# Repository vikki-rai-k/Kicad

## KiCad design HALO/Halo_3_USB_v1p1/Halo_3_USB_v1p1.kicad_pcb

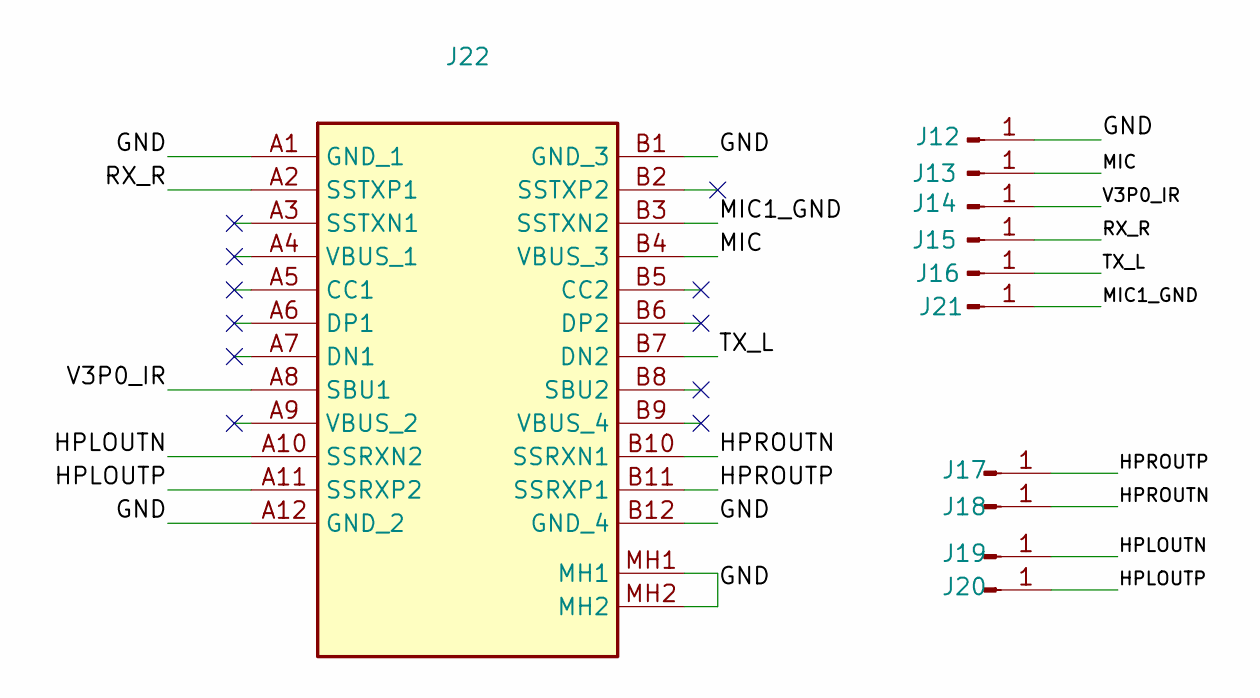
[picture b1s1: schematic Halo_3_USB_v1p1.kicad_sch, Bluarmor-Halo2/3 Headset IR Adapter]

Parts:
J12, J13, J14, J15, J16, J17, J18, J19, J20, J21: Conn_01x01_Pin; Test_Point_1.5mm_SMD_Tiny
J22: Shouhan_TypeC_24_vertical; Mouser Part Number 523-GSB3CN1130DSHR

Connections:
/GND: J12.1, J22.A1 (GND_1), J22.A12 (GND_2), J22.B1 (GND_3), J22.B12 (GND_4), J22.MH1, J22.MH2
/HPLOUTN: J19.1, J22.A10 (SSRXN2)
/HPLOUTP: J20.1, J22.A11 (SSRXP2)
/HPROUTN: J18.1, J22.B10 (SSRXN1)
/HPROUTP: J17.1, J22.B11 (SSRXP1)
/MIC: J13.1, J22.B4 (VBUS_3)
/MIC1_GND: J21.1, J22.B3 (SSTXN2)
/RX_R: J15.1, J22.A2 (SSTXP1)
/TX_L: J16.1, J22.B7 (DN2)
/V3P0_IR: J14.1, J22.A8 (SBU1)

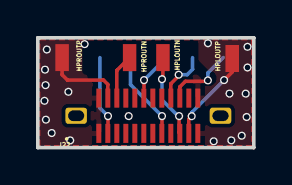
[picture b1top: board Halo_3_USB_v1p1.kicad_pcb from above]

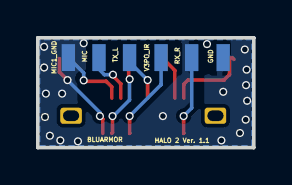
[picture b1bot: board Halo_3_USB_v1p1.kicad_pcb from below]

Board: 2 copper layers, 12.0 x 6.1 mm, 11 parts (6 on the bottom side), 10 nets.

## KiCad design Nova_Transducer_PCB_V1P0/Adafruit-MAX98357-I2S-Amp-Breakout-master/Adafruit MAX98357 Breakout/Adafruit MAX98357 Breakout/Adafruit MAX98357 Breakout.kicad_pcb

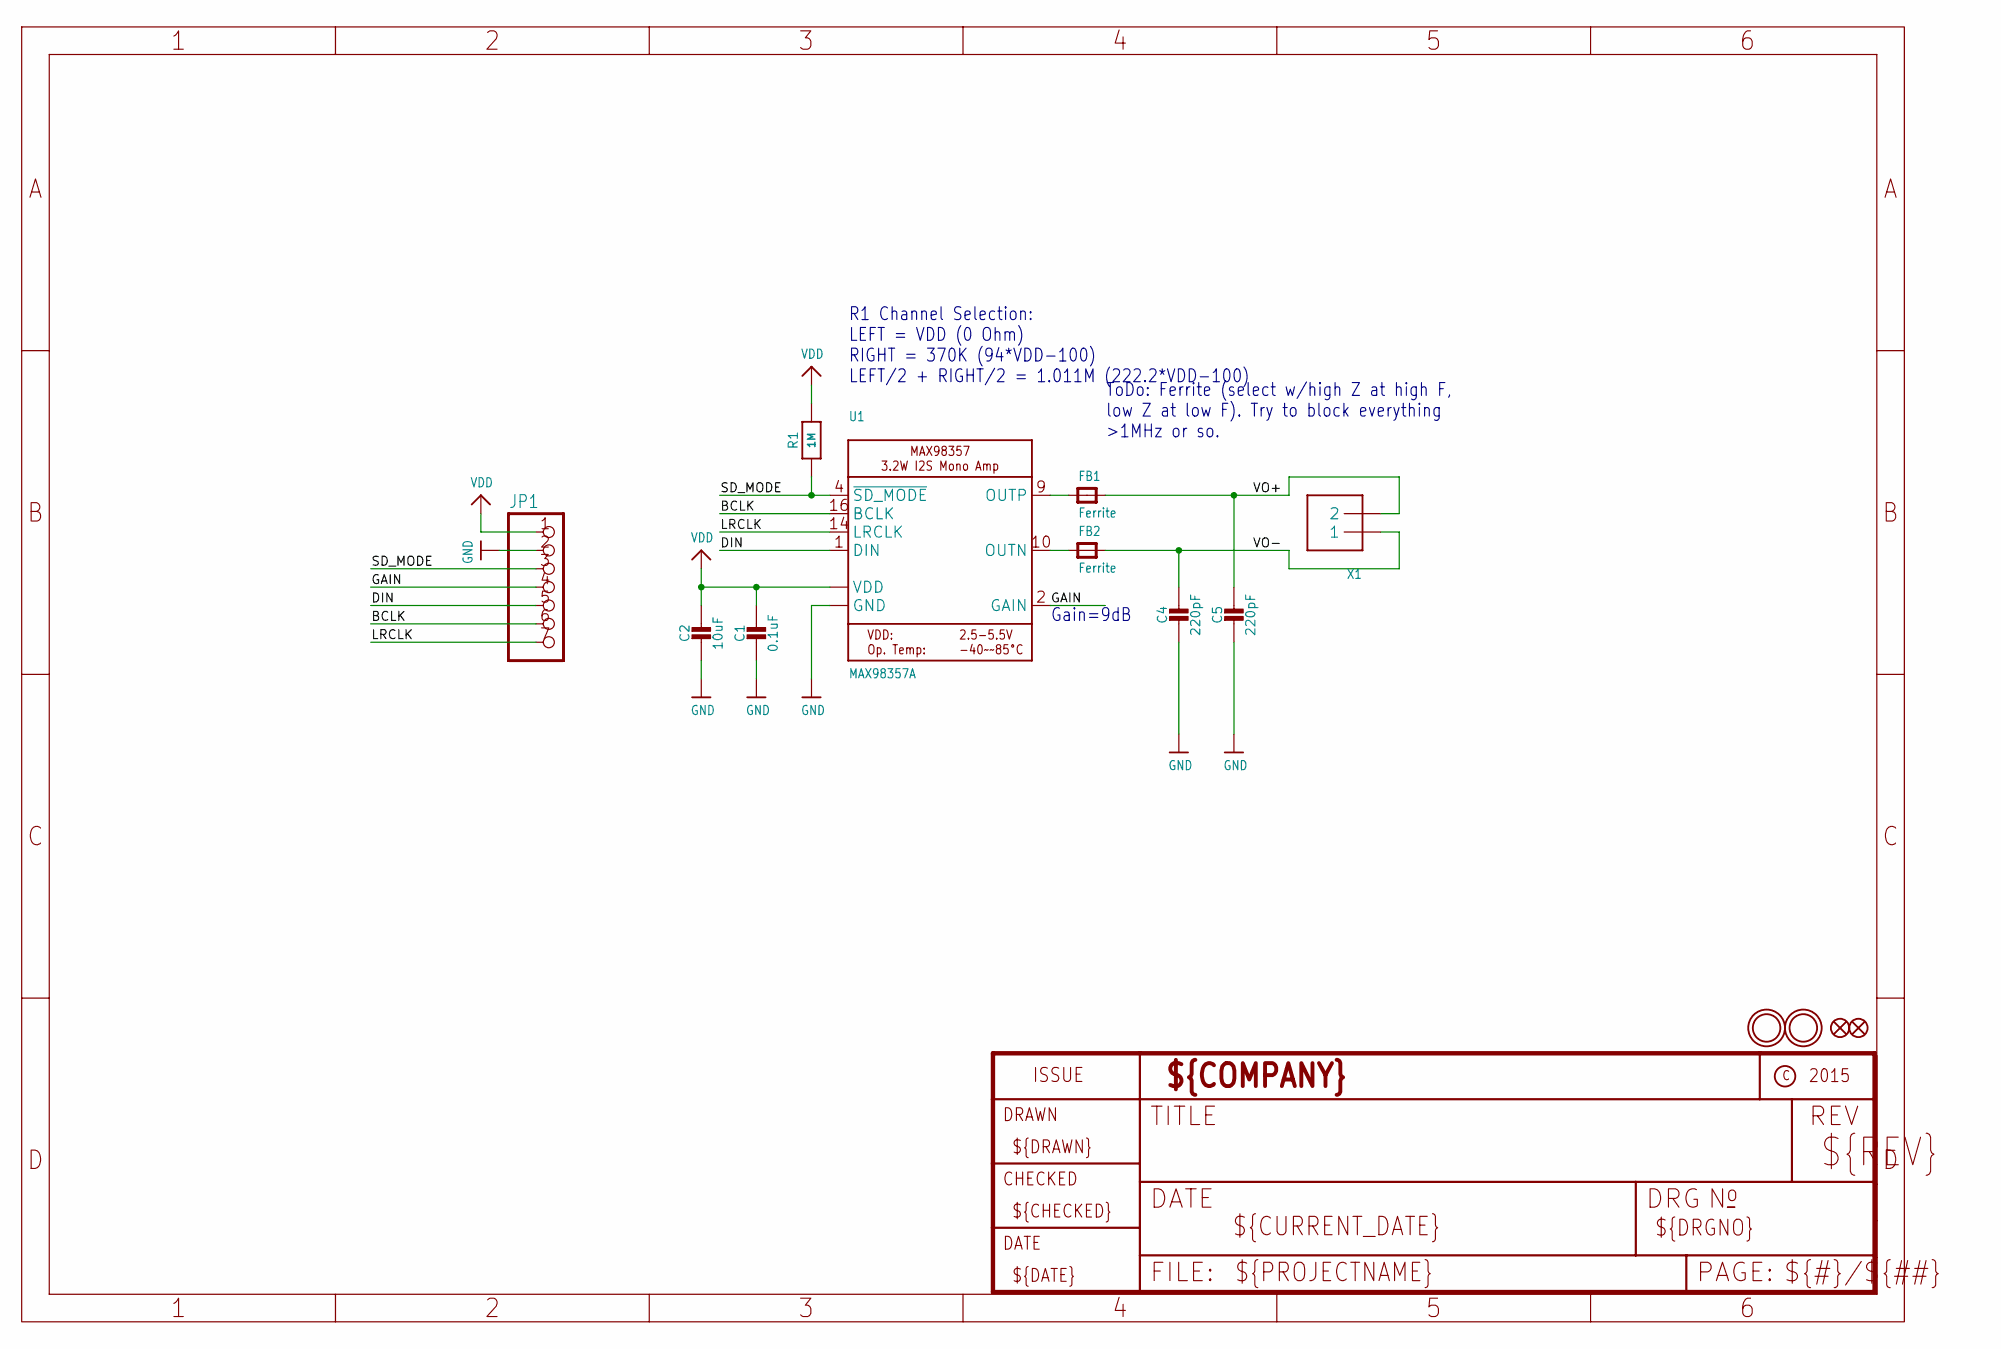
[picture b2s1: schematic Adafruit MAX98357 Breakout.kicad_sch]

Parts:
C1: 0.1uF; 0805-NO
C2: 10uF; 0805-NO
C4, C5: 220pF; 0805-NO
FB1, FB2: Ferrite; 0805-NO
FID1, FID2: FIDUCIAL""; FIDUCIAL_1MM
JP1: HEADER-1X7THICKER; 1X07_ROUND_76
R1: 1M; 0805-NO
U1: MAX98357A; QFN16_3MM
U$9, U$10: MOUNTINGHOLE2.5; MOUNTINGHOLE_2.5_PLATED
X1: TERMBLOCK_1X2; TERMBLOCK_1X2-3.5MM

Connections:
BCLK: JP1.6, U1.16 (BCLK)
DIN: JP1.5, U1.1 (DIN)
GAIN: JP1.4, U1.2 (GAIN)
GND: C1.2, C2.2, C4.2, C5.2, JP1.2, U1.3 (GND), U1.11 (GND), U1.15 (GND), U1.THERMAL (GND)
LRCLK: JP1.7, U1.14 (LRCLK)
unnamed: FB2.1, U1.10 (OUTN)
unnamed: FB1.1, U1.9 (OUTP)
SD_MODE: JP1.3, R1.1, U1.4 (~SD_MODE)
VDD: C1.1, C2.1, JP1.1, R1.2, U1.7 (VDD), U1.8 (VDD)
VO+: C5.1, FB1.2, X1.2
VO-: C4.1, FB2.2, X1.1

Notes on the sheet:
Gain=9dB
R1 Channel Selection: LEFT = VDD (0 Ohm) RIGHT = 370K (94*VDD-100) LEFT/2 + RIGHT/2 = 1.011M (222.2*VDD-100)
ToDo: Ferrite (select w/high Z at high F, low Z at low F). Try to block everything >1MHz or so.

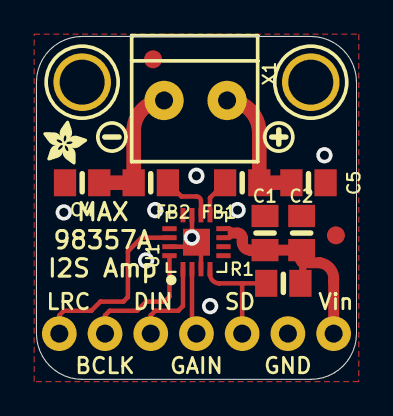
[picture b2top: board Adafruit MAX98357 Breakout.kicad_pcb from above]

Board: 2 copper layers, 17.8 x 19.0 mm, 18 parts (1 on the bottom side), 11 nets.

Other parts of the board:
U$6: SYMBOL_PLUS
U$11: SYMBOL_MINUS
U$14: ADAFRUIT_2.5MM
U$15: PCBFEAT-REV-040

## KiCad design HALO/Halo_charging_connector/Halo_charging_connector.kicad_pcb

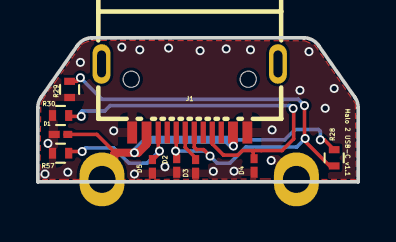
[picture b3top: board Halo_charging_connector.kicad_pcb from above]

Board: 2 copper layers, 17.8 x 8.0 mm, 12 parts (0 on the bottom side), 6 nets.

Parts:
D1, D2, D3, D4, D5: ESD5451X2TR
J1: TYPE-C 16PFS 2JCB1.6-H7.45 IPX8; USB-SMD_TYPE-C-16PFS-2J-H7.45-IPX8
R28: 60.4K; R_0402
R29: 10K; R_0402
R30, R57: 5.1K; R_0402
U1, U2: -; Halo_2_USBC_Charging_PCB_Castellated_holes

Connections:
/CC1: D4.2 (A2), J1.A5 (CC1), R30.1
/CC2: D5.2 (A2), J1.B5 (CC2), R57.1
/DN: D3.2 (A2), J1.A7 (DA_N)
/DP: D2.2 (A2), J1.A6 (DA_P), J1.B6 (DB_P), R28.2, R29.1
/GND: D1.1 (A1), D2.1 (A1), D3.1 (A1), D4.1 (A1), D5.1 (A1), J1.B1A12 (GNDB), J1.B12A1 (GNDA), R29.2, R30.2, R57.2, U2.1
/VUSB: D1.2 (A2), J1.A4B9 (VBUS_A), J1.A9B4 (VBUS_B), R28.1, U1.1

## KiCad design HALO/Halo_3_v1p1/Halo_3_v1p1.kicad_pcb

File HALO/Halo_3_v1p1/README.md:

# MagnaRox

## Getting started

To make it easy for you to get started with GitLab, here's a list of recommended next steps.

Already a pro? Just edit this README.md and make it your own. Want to make it easy? [Use the template at the bottom](#editing-this-readme)!

## Add your files

- [ ] [Create](https://docs.gitlab.com/ee/user/project/repository/web_editor.html#create-a-file) or [upload](https://docs.gitlab.com/ee/user/project/repository/web_editor.html#upload-a-file) files
- [ ] [Add files using the command line](https://docs.gitlab.com/ee/gitlab-basics/add-file.html#add-a-file-using-the-command-line) or push an existing Git repository with the following command:

```
cd existing_repo
git remote add origin https://gitlab.com/bluarmor_hw_dev/magnarox.git
git branch -M main
git push -uf origin main
```

## Integrate with your tools

- [ ] [Set up project integrations](https://gitlab.com/bluarmor_hw_dev/magnarox/-/settings/integrations)

## Collaborate with your team

- [ ] [Invite team members and collaborators](https://docs.gitlab.com/ee/user/project/members/)
- [ ] [Create a new merge request](https://docs.gitlab.com/ee/user/project/merge_requests/creating_merge_requests.html)
- [ ] [Automatically close issues from merge requests](https://docs.gitlab.com/ee/user/project/issues/managing_issues.html#closing-issues-automatically)
- [ ] [Enable merge request approvals](https://docs.gitlab.com/ee/user/project/merge_requests/approvals/)
- [ ] [Set auto-merge](https://docs.gitlab.com/ee/user/project/merge_requests/merge_when_pipeline_succeeds.html)

## Test and Deploy

Use the built-in continuous integration in GitLab.

- [ ] [Get started with GitLab CI/CD](https://docs.gitlab.com/ee/ci/quick_start/index.html)
- [ ] [Analyze your code for known vulnerabilities with Static Application Security Testing(SAST)](https://docs.gitlab.com/ee/user/application_security/sast/)
- [ ] [Deploy to Kubernetes, Amazon EC2, or Amazon ECS using Auto Deploy](https://docs.gitlab.com/ee/topics/autodevops/requirements.html)
- [ ] [Use pull-based deployments for improved Kubernetes management](https://docs.gitlab.com/ee/user/clusters/agent/)
- [ ] [Set up protected environments](https://docs.gitlab.com/ee/ci/environments/protected_environments.html)

***

# Editing this README

When you're ready to make this README your own, just edit this file and use the handy template below (or feel free to structure it however you want - this is just a starting point!). Thank you to [makeareadme.com](https://www.makeareadme.com/) for this template.

## Suggestions for a good README
Every project is different, so consider which of these sections apply to yours. The sections used in the template are suggestions for most open source projects. Also keep in mind that while a README can be too long and detailed, too long is better than too short. If you think your README is too long, consider utilizing another form of documentation rather than cutting out information.

## Name
Choose a self-explaining name for your project.

## Description
Let people know what your project can do specifically. Provide context and add a link to any reference visitors might be unfamiliar with. A list of Features or a Background subsection can also be added here. If there are alternatives to your project, this is a good place to list differentiating factors.

## Badges
On some READMEs, you may see small images that convey metadata, such as whether or not all the tests are passing for the project. You can use Shields to add some to your README. Many services also have instructions for adding a badge.

## Visuals
Depending on what you are making, it can be a good idea to include screenshots or even a video (you'll frequently see GIFs rather than actual videos). Tools like ttygif can help, but check out Asciinema for a more sophisticated method.

## Installation
Within a particular ecosystem, there may be a common way of installing things, such as using Yarn, NuGet, or Homebrew. However, consider the possibility that whoever is reading your README is a novice and would like more guidance. Listing specific steps helps remove ambiguity and gets people to using your project as quickly as possible. If it only runs in a specific context like a particular programming language version or operating system or has dependencies that have to be installed manually, also add a Requirements subsection.

## Usage
Use examples liberally, and show the expected output if you can. It's helpful to have inline the smallest example of usage that you can demonstrate, while providing links to more sophisticated examples if they are too long to reasonably include in the README.

## Support
Tell people where they can go to for help. It can be any combination of an issue tracker, a chat room, an email address, etc.

## Roadmap
If you have ideas for releases in the future, it is a good idea to list them in the README.

## Contributing
State if you are open to contributions and what your requirements are for accepting them.

For people who want to make changes to your project, it's helpful to have some documentation on how to get started. Perhaps there is a script that they should run or some environment variables that they need to set. Make these steps explicit. These instructions could also be useful to your future self.

You can also document commands to lint the code or run tests. These steps help to ensure high code quality and reduce the likelihood that the changes inadvertently break something. Having instructions for running tests is especially helpful if it requires external setup, such as starting a Selenium server for testing in a browser.

## Authors and acknowledgment
Show your appreciation to those who have contributed to the project.

## License
For open source projects, say how it is licensed.

## Project status
If you have run out of energy or time for your project, put a note at the top of the README saying that development has slowed down or stopped completely. Someone may choose to fork your project or volunteer to step in as a maintainer or owner, allowing your project to keep going. You can also make an explicit request for maintainers.

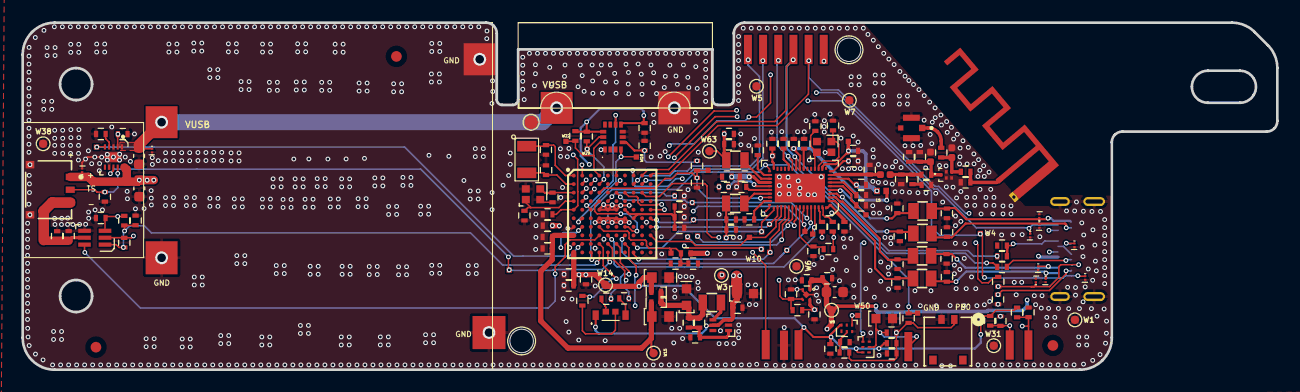
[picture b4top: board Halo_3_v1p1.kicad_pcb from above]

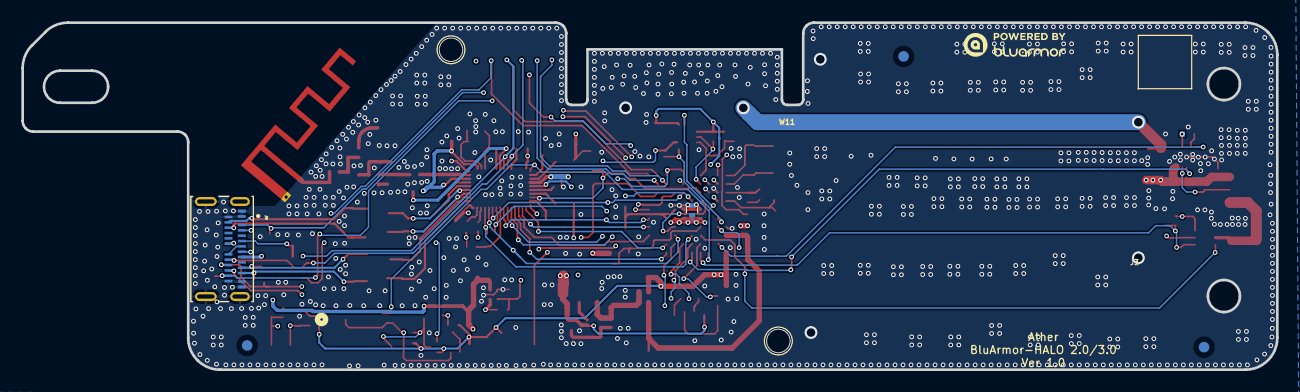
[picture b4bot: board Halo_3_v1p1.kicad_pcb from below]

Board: 4 copper layers, 117.5 x 32.5 mm, 234 parts (7 on the bottom side), 103 nets.

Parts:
C1, C2, C15, C18, C46: 4.7uF/10V; C_0402
C3, C21, C78, C80: 1uF; C_0402
C4, C33, C37: 10uF/10V; GRM188R61A106KE69D
C5, C6, C11, C14, C16, C17, C22, C41, C48, C51, C52, C56, C68, C69, C106: 1uF/10V; C_0402
C7, C23, C25, C29, C30, C31, C32, C35, C40, C42, C45, C60, C64, C67, C76, C81, C85, C98, C101, C102, C103, C111: 100nF; C_0402
C8, C43: 2.2uF/16V; C_0402
C9, C10: 100nF/10V; C_0402
C12, C13: 8pF; C_0402
C19, C28: 22uF/10V; GRM188R61A226ME15D
C20, C24: 8.2pF; C_0402
C26, C27: 12pF; C_0402
C34: 6.8pF; C_0402
C36, C39: 2.2uF; C_0402
C38: 330nF; C_0402
C44, C57: 1.3pF/50V; C_0402
C47: 0.6pF/50V; C_0402
C49: 1uF/25V; C_0603_1608Metric
C50: 10uF/10V; C_0603_1608Metric
C53, C58: 1pF; C_0402
C75: 10uF; C_0603_1608Metric
C95: 0.3pF; C_0402
C99, C100, C104, C105: 680pF/6.3V; C_0402
D4, D5, D16, D20, D21, D22, D23, D24, D25, D26: ESD_ST_ESDZV5H_1BU2; ESDZV5H-1BU2
D27: 155124M173200
F1, F2, F3, F4, F5, F6: Fiducial; Fiducial_1mm_Mask2mm
FL2: HS5524EB06; QPQ1907
H6, H7: MountingHoleCircle; MountingHole_Circle_2.2mm
J1, J5, J6, J7, J16, J19, J20, J21, J22, J30, J31, J301: TEST_1P_2p75_0p75; Test_Point_0.75mmby2.75mm_SMD_Tiny
J8: BM02B-ACHSS-GAN-ETFLFSN
J9: 2305018-2; TE_2305018-2_MountingHole_0.4mm
J12: BM03B-ACHSS-GAN-ETF
J23: KH-IPEX4-2020
J24, J25, J26, J27, J28, J29: TEST_1P_2p75_0p75; Castellated_pads_3mm
L1, L7, L10, L11: 10UH 250MA 1.05OHM; CKP2012N2R2M-T
L2, L3: Ferrite_Bead; BKP1005HS100-T
L4: 2.2uH/0.5A/1MHz; CKP2012N2R2M-T
L5: BLM15AG601SN1D; BEADC1005X55N
L6, L23: 2.2uH/0.75A/1MHz; CKP2012N2R2M-T
L12: 2.7nH; L_0402_0201
L17, L18: 5.6nH; L_0402_0201
QR2: Laser_QR_5x5
R1, R11, R12, R21, R23, R25, R27, R28, R29, R34, R38: 0; R_0402
R2, R4: 1M; R_0402
R3, R17: 330; R_0402
R5, R6, R7, R26: 22K; R_0402
R8: 22k; R_0402
R9, R40: 215K; R_0402
R10: 100K; R_0402
R15, R31: 100k; R_0402
R16, R33: 510k; R_0402
R37: 500; R_0402
R41: 1.8K; R_0402
R49: 680; R_0402
R51: 2K; R_0402
R52: 249K; R_0402
R78, R79: 2.2K; R_0402
Rs1, Rs2: 10m/0.0625W; R_0402
T1, T2, T3, T4, T5, T6, T7, T8, T9, T10, T11, T12: Tab
U1: 74AUP1G14DRY; PSON50P145X100X60-6N
U2: 74LVC1G17; PSON50P145X100X60-6N
U3: BQ24040DSQR; SON40P200X200X80-11N
U5: INA199A1DCKR; SOT65P210X110-6N
U6: RTL8763EAU_QFN50; QFN-50-1EP_4x6mm_P0.35mm_EP2.7x4.7mm_ESL
U8: TLV62568DRLR; SOT50P160X60-6N
U13: TLV74330PDQNR; SUP_TPS3831L30DQNR
U19: LSM6DSLTR
U23: BT_ANT; TI_IIFA_2p4GHz_tuned_Magnarox
U344: STM32H7A3VGH6; BGA100C80P10X10_800X800X110
W1, W5, W6, W7, W8, W31, W38: TEST_1P; Test_Point_0.8mmDia_SMD_Tiny
W3, W14, W15, W63: T1P; Test_Point_0.8mmDia_SMD_Tiny
W4, W9, W10, W12, W18, W19, W20, W22, W28, W29, W33, W34, W35, W45, W46, W47, W48, W50, W51, W52, W55, W57, W58, W59, W60, W61, W65: T1P; TestPoint_Square_0.5_SMD_Tiny
W11: T1P; Test_Point_1.3mmDia_SMD_Tiny
X1: 26MHz; XTALDFN200X160X70-4N
X3: 40MHz; XTALDFN200X160X70-4N
Y2: 32.768kHz; FC-135

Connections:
/ACCL_INT1: U19.4 (INT1), U344.F2 (PC1), W18.1
/ACCL_INT2: U19.9 (INT2), U344.E3 (PE6)
/BAT_TS: J12.2, R52.2, U3.9 (TS)
/BT_BLE/ADPSO: C18.1, U6.27 (ADPSO)
/BT_BLE/AOUT_LN: C100.1, L11.1, U6.3 (AOUT_LN)
/BT_BLE/AOUT_LP: C99.1, L10.1, U6.2 (AOUT_LP)
/BT_BLE/AOUT_RN: C104.1, L1.1, U6.4 (AOUT_RN)
/BT_BLE/AOUT_RP: C105.1, L7.1, U6.5 (AOUT_RP)
/BT_BLE/AVCC: C5.1, U6.6 (AVCC), W61.1
/BT_BLE/AVCC_CODEC: C2.1, C7.2, C11.1, L6.2, U6.1 (AVCC_DRV), U6.50 (AVCC_DRV), W59.1
/BT_BLE/HV: C46.1, U6.31 (HV)
/BT_BLE/HV33: C16.1, U6.21 (LDO33)
/BT_BLE/LX_AUDIO: L6.1, U6.32 (LX_AUDIO)
/BT_BLE/LX_CORE: L23.1, U6.28 (LDO12/LX_CORE)
/BT_BLE/MIC1_N: C106.1, U6.48 (MIC1_N)
/BT_BLE/MIC1_P: C48.1, U6.49 (MIC1_P)
/BT_BLE/MIC_BIAS: C17.1, R41.2, U6.43 (MICBIAS)
/BT_BLE/RTL_DIG_OUT: C14.1, U6.17 (DIG_OUT)
/BT_BLE/RTL_RF_ANT: R1.2, R38.1, U23.1 (FEED)
/BT_BLE/RTL_RF_BPF_OUT: FL2.4 (OUTPUT), L18.2, R25.1, R38.2
/BT_BLE/RTL_RF_OUT: C57.2, C58.1, C95.1, FL2.1 (INPUT), L17.2
/BT_BLE/RTL_RF_RFIO_IQM: C44.1, L12.1, U6.9 (RFIO_IQM)
/BT_BLE/RTL_RF_RFIQ_MAT: C47.1, C53.1, C57.1, L12.2
/BT_BLE/RTL_XI: C12.1, U6.13 (XI), X3.1
/BT_BLE/RTL_XO: C13.1, U6.14 (XO), X3.3
/BT_BLE/VD12_RF: C8.1, C10.1, L5.2, U6.8 (VD12_RTX), U6.12 (VD12_SYN), W60.1
/BT_BLE/VDDCORE: C1.1, C15.1, C85.1, L5.1, L23.2, U6.18 (VDDCORE), W63.1
/BT_BLE/VDD_3V3: C9.1, C22.1, U6.10 (VD33_PA), U6.25 (VPA33), W65.1
/BT_BLE/VDD_ADP: C43.1, U6.30 (ADPIN)
/BT_BLE/VDD_LDO_AUX: C56.1, U6.34 (LDO_AUX)
/BT_BLE/VREF: C6.1, U6.7 (CPVREF)
/Battery Management/ASI_1: R51.2, U3.4 (PRETERM)
/Battery Management/ISET_1: R49.2, U3.2 (ISET), W12.1
/DEBUG_RX: J5.1, U344.B8 (PC11)
/DEBUG_TX: J16.1, U344.B9 (PC10)
/HPLOUTN: C69.1, D25.1 (A1), J9.A10 (RX2_N), L11.2
/HPLOUTP: C68.1, D26.1 (A1), J9.A11 (RX2_P), L10.2
/HPROUTN: C51.1, D24.1 (A1), J9.B10 (RX1_N), L1.2
/HPROUTP: C52.1, D23.1 (A1), J9.B11 (RX1_P), L7.2
/I2C4_M_SCL: R79.1, U19.13 (SCL), U344.B4 (PB8), W29.1
/I2C4_M_SDA: R78.1, U19.14 (SDA), U344.A4 (PB9), W22.1
/IBAT_MON: U5.6 (OUT), U344.H4 (PC5)
/IR_RX_L: C29.2, D21.1 (A1), J9.B2 (TX2_P), J30.1, R6.2, U344.B3 (PE3), W4.1
/IR_RX_R: D20.1 (A1), J9.A2 (TX1_P), U344.C3 (PE4)
/IR_TX_L: D16.1 (A1), J9.B7 (DB_N), U344.E10 (PC7), W10.1
/IR_TX_R: C42.2, J9.A7 (DA_N), J31.1, R7.2, U344.D4 (PE0), U344.G7 (PE14)
/LDO_3V_EN: R12.2, R40.1, U13.3 (EN), U344.C9 (PA9)
/MCU/BOOT0: R8.1, U344.D5 (BOOT0)
/MCU/CLKIN_26MHz: C26.1, U344.C1 (PH0-OSC_IN), X1.1
/MCU/CLKOUT_26MHz: C27.1, U344.D1 (PH1-_OSC_OUT), X1.3
/MCU/J4: R17.2, U344.J4 (PB0)
/MCU/J5: R37.2, U344.J5 (PE8)
/MCU/J6: R3.2, U344.J6 (PE12)
/MCU/Sheet61738EA9/LED_B3: D27.2 (BLUE), R3.1
/MCU/Sheet61738EA9/LED_G3: D27.3 (GRREN), R17.1
/MCU/Sheet61738EA9/LED_R3: D27.4 (RED), R37.1
/MCU/VCAP: C36.2, C39.2, C103.1, U344.E7 (VCAP), U344.F8 (VCAP)
/MCU/Xtal_32k_in: C24.1, U344.A1 (PC14-OSC32_IN), Y2.1
/MCU/Xtal_32k_out: C20.1, U344.B1 (PC15-OSC32_OUT), Y2.2
/MIC: C48.2, D22.1 (A1), J9.B4 (VBUS_B), R34.2, R41.1
/MICGND: C106.2, J9.B3 (TX2_N), R27.2
/Main Connector/CC1: J9.A5 (CC1), R23.2, R28.2
/Main Connector/CC2: J9.B5 (CC2), R21.2
/Main Connector/DP: J9.A6 (DA_P), J9.B6 (DB_P)
/Main Connector/~PB1_10Sec: C4.1, J6.1, R4.1, U2.2 (A)
/Main Connector/~PB1_FILT: C3.1, R2.1, U1.2 (A)
/PowerManagement/1V8_SW: L4.1, U8.4 (SW)
/PowerManagement/VDD: C33.1, C34.1, L2.1, L3.1, L4.2, R9.1
/PowerManagement/VDD_FB: C34.2, R9.2, R10.1, U8.1 (FB)
/RF_UFL_CON: J23.1, R25.2
/RTL_GPIO1: U6.45 (MIC3_P), U344.C6 (PD6), W52.1
/RTL_GPIO2: U6.46 (MIC2_N/AUXL), U344.H7 (PE15), W55.1
/RTL_HCI_UART_TX: J301.1, R21.1, U6.20 (P3_1)
/RTL_HW_RST_N: C60.2, R26.2, U6.33 (HW_RST_N), U344.C4 (PE1), W48.1
/RTL_LOGGER_PIN: U6.42 (ADC_3), U344.F10 (PC6), W45.1
/RTL_MFB_N: R29.1, U6.26 (MFB), U344.K3 (PA7), W57.1
/RTL_MODE: J1.1, U6.35 (P2_0)
/RTL_SPI_CLK: U6.40 (ADC_1), U344.C7 (PD3), W28.1
/RTL_SPI_CS: U6.41 (ADC_2), U344.A6 (PB4), U344.A8 (PA15), W33.1
/RTL_SPI_M2S_GPIO: U6.47 (MIC2_P/AUXR), U344.H5 (PE7), W58.1
/RTL_SPI_MISO: U6.38 (P2_3), U344.H10 (PB14), W34.1
/RTL_SPI_MOSI: U6.37 (P2_2), U344.G10 (PB15), W35.1
/RTL_SPI_S2M_GPIO: U6.44 (MIC3_N), U344.B6 (PD5), W51.1
/RTL_UART_ST_RX: U6.39 (ADC_0), U344.K8 (PB12), W47.1
/RTL_UART_ST_TX: U6.36 (P2_1), U344.J8 (PB13), W46.1
/ST_SWDIO: J20.1, R34.1, U344.A10 (PA13)
/SWDCLK: J19.1, R28.1, U6.19 (P3_0), U344.A9 (PA14)
/V3P0: C23.1, C75.1, C76.1, C78.1, J9.A8 (SBU1), R33.2, U5.3 (V+), U13.1 (OUT), W8.1
/VBAT+: C35.1, C37.1, C41.1, C50.1, C80.1, C98.1, D5.1 (A1), D27.1 (VDD), J12.1, R12.1, R16.2, U3.10 (OUT), U6.29 (VBAT), U8.3 (VIN), U8.5 (EN), U13.4 (IN), W3.1
/VBAT-: J12.3, Rs1.2, Rs2.2, U5.5 (IN-)
/VBAT_MON: C64.1, R15.1, R16.1, U344.G4 (PC4), W19.1
/VDD_A: C21.1, C28.1, C31.2, L2.2, U344.H1 (VDDA), W15.1
/VDD_D: C19.1, C25.2, C30.2, C32.2, C40.2, C81.1, C101.2, C102.2, C111.2, J22.1, L3.2, R5.1, R6.1, R7.1, R26.1, R78.2, R79.2, U1.6 (VCC), U2.6 (VCC), U19.5 (VDDIO), U19.8 (VDD), U19.12 (CS), U344.B2 (VBAT), U344.D2 (VDD), U344.F4 (VDD), U344.F5 (VDD), U344.F6 (VDD33USB), U344.F7 (PDR_ON), U344.K1 (VDD), W14.1
/VREF_IBAT_MON: C67.1, R31.2, R33.1, U5.1 (REF), U344.K4 (PB1)
/VUSB: C49.2, D4.1 (A1), J24.1, J28.1, U3.1 (IN), W11.1
/WakeUp_PB1: U1.4 (Y), U344.G2 (PA0), W50.1
/nRST_TP: C38.2, J9.A3 (TX1_N), J21.1, U2.4 (Y), U344.E1 (NRST)
/~BAT_CHG_INT: U3.8 (~CHG), U344.K5 (PE9), W9.1
/~EN_CUR_SENSE: R31.1, U5.2 (GND), U344.J7 (PB10)
/~PB1: C45.2, J8.1, R2.2, R4.2, R5.2, R29.2, U344.A2 (PC13)
/~PG: U3.5 (~PG), U344.J2 (PA2), W20.1
GND: C1.2, C2.2, C3.2, C4.2, C5.2, C6.2, C7.1, C8.2, C9.2, C10.2, C11.2, C12.2, C13.2, C14.2, C15.2, C16.2, C17.2, C18.2, C19.2, C20.2, C21.2, C22.2, C23.2, C24.2, C25.1, C26.2, C27.2, C28.2, C29.1, C30.1, C31.1, C32.1, C33.2, C35.2, C36.1, C37.2, C38.1, C39.1, C40.1, C41.2, C42.1, C43.2, C44.2, C45.1, C46.2, C49.1, C50.2, C51.2, C52.2, C53.2, C56.2, C58.2, C60.1, C64.2, C67.2, C68.2, C69.2, C75.2, C76.2, C78.2, C80.2, C81.2, C85.2, C95.2, C98.2, C99.2, C100.2, C101.1, C102.1, C103.2, C104.2, C105.2, C111.1, D4.2 (A2), D5.2 (A2), D16.2 (A2), D20.2 (A2), D21.2 (A2), D22.2 (A2), D23.2 (A2), D24.2 (A2), D25.2 (A2), D26.2 (A2), FL2.2 (GND_1), FL2.3 (GND_2), FL2.5 (GND_3), J7.1, J8.2, J9.A1 (GNDA), J9.A12 (GNDA), J9.B1 (GNDB), J9.B12 (GNDB), J9.G1 (GND), J9.G2 (GND), J9.S1 (SHIELD), J9.S2 (SHIELD), J9.S3 (SHIELD), J9.S4 (SHIELD), J12.4 (MNT_1), J12.5 (MNT_2), J23.S1, J25.1, J26.1, J27.1, J29.1, L17.1, L18.1, R1.1, R8.2, R10.2, R11.2, R15.2, R27.1, R40.2, R49.1, R51.1, R52.1, Rs1.1, Rs2.1, U1.3 (GND), U2.3 (GND), U3.3 (VSS), U3.7 (ISET2), U3.11 (EXP), U5.4 (IN+), U6.51 (EPAD), U8.2 (GND), U13.2 (GND), U13.5 (EP), U19.1 (SDO/SA0), U19.6 (GND_1), U19.7 (GND_2), U23.2 (GND), U344.C2 (VSS), U344.E4 (VSS), U344.E5 (VSS), U344.E6 (VSS), U344.G1 (VSSA), U344.J1 (VSS), W1.1, W5.1, W6.1, W7.1, W31.1, W38.1, X1.2, X1.4, X3.2, X3.4
unnamed: C47.2, R11.1

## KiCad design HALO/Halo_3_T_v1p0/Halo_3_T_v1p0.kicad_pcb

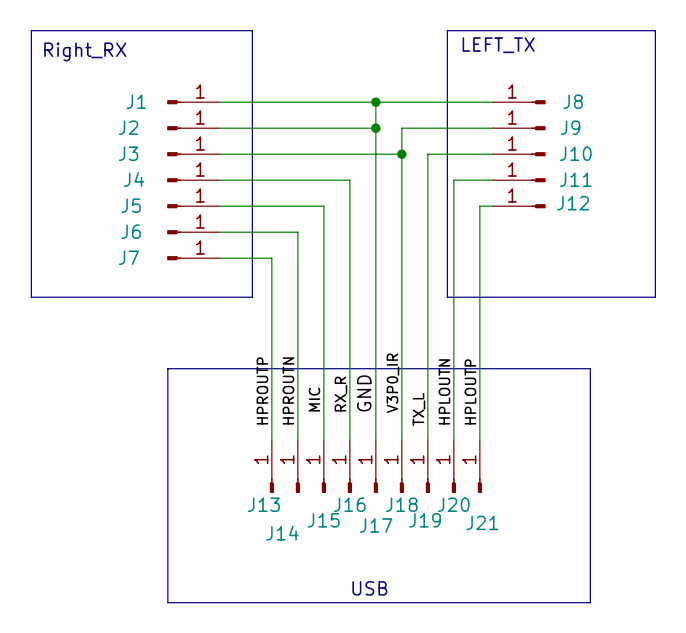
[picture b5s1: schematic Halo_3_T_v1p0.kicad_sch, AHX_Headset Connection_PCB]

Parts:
J1, J2, J3, J4, J5, J6, J7, J8, J9, J10, J11, J12, J13, J14, J15, J16, J17, J18, J19, J20, J21: Conn_01x01_Pin; AHX30_HeadSet_T_Junction_Pad_1.5 x 1.5 dia 0.3

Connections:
/GND: J1.1, J2.1, J8.1, J17.1
/HPLOUTN: J11.1, J20.1
/HPLOUTP: J12.1, J21.1
/HPROUTN: J6.1, J14.1
/HPROUTP: J7.1, J13.1
/MIC: J5.1, J15.1
/RX_R: J4.1, J16.1
/TX_L: J10.1, J19.1
/V3P0_IR: J3.1, J9.1, J18.1

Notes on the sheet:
LEFT_TX
USB
Right_RX

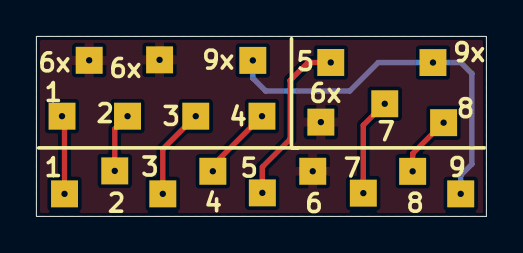
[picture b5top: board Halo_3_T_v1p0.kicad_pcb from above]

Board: 2 copper layers, 25.0 x 10.0 mm, 21 parts (0 on the bottom side), 9 nets.

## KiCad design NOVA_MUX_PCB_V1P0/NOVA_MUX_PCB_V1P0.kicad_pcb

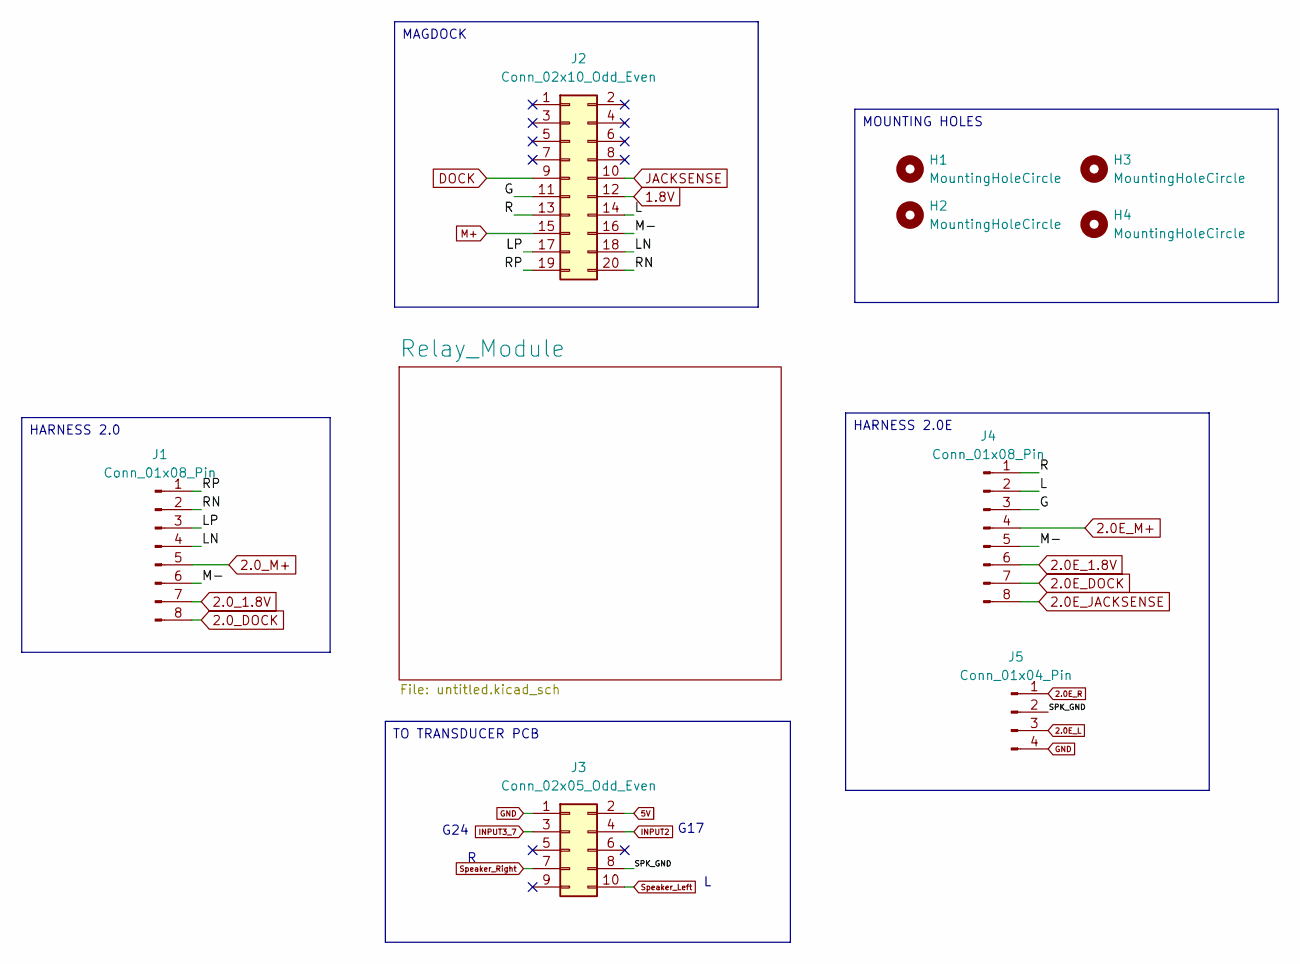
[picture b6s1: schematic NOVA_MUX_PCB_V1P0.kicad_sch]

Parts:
H1, H2, H3, H4: MountingHoleCircle; MountingHole_3.2mm_M3
J1, J4: Conn_01x08_Pin; JST_EH_B8B-EH-A_1x08_P2.50mm_Vertical; mpn 8 Pin JST-XH Male Straight 2515 Connect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
J2: Conn_02x10_Odd_Even; PinSocket_2x10_P2.54mm_Vertical; mpn 20 Pin Straight Male IDC Socket Connect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
J3: Conn_02x05_Odd_Even; PinHeader_2x05_P2.54mm_Vertical; mpn 10 Pin Straight Male IDC Socket Connect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
J5: Conn_01x04_Pin; JST_EH_B4B-EH-A_1x04_P2.50mm_Vertical; mpn 4 Pin JST-XH Male Straight 2515 Connect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

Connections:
1.8V: J2.12; also elsewhere on the board
2.0E_1.8V: J4.6; also elsewhere on the board
2.0E_DOCK: J4.7; also elsewhere on the board
2.0E_JACKSENSE: J4.8; also elsewhere on the board
2.0E_L: J5.3; also elsewhere on the board
2.0E_M+: J4.4; also elsewhere on the board
2.0E_R: J5.1; also elsewhere on the board
2.0_1.8V: J1.7; also elsewhere on the board
2.0_DOCK: J1.8; also elsewhere on the board
2.0_M+: J1.5; also elsewhere on the board
5V: J3.2; also elsewhere on the board
/G: J2.11, J4.3
/L: J2.14, J4.2
/LN: J1.4, J2.18
/LP: J1.3, J2.17
/M-: J1.6, J2.16, J4.5
/R: J2.13, J4.1
/RN: J1.2, J2.20
/RP: J1.1, J2.19
/SPK_GND: J3.8, J5.2
DOCK: J2.9; also elsewhere on the board
GND: J3.1, J5.4; also elsewhere on the board
INPUT2: J3.4; also elsewhere on the board
INPUT3_7: J3.3; also elsewhere on the board
JACKSENSE: J2.10; also elsewhere on the board
M+: J2.15; also elsewhere on the board
Speaker_Left: J3.10; also elsewhere on the board
Speaker_Right: J3.7; also elsewhere on the board

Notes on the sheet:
G17
G24
TO TRANSDUCER PCB
HARNESS 2.0E
HARNESS 2.0
MOUNTING HOLES
MAGDOCK

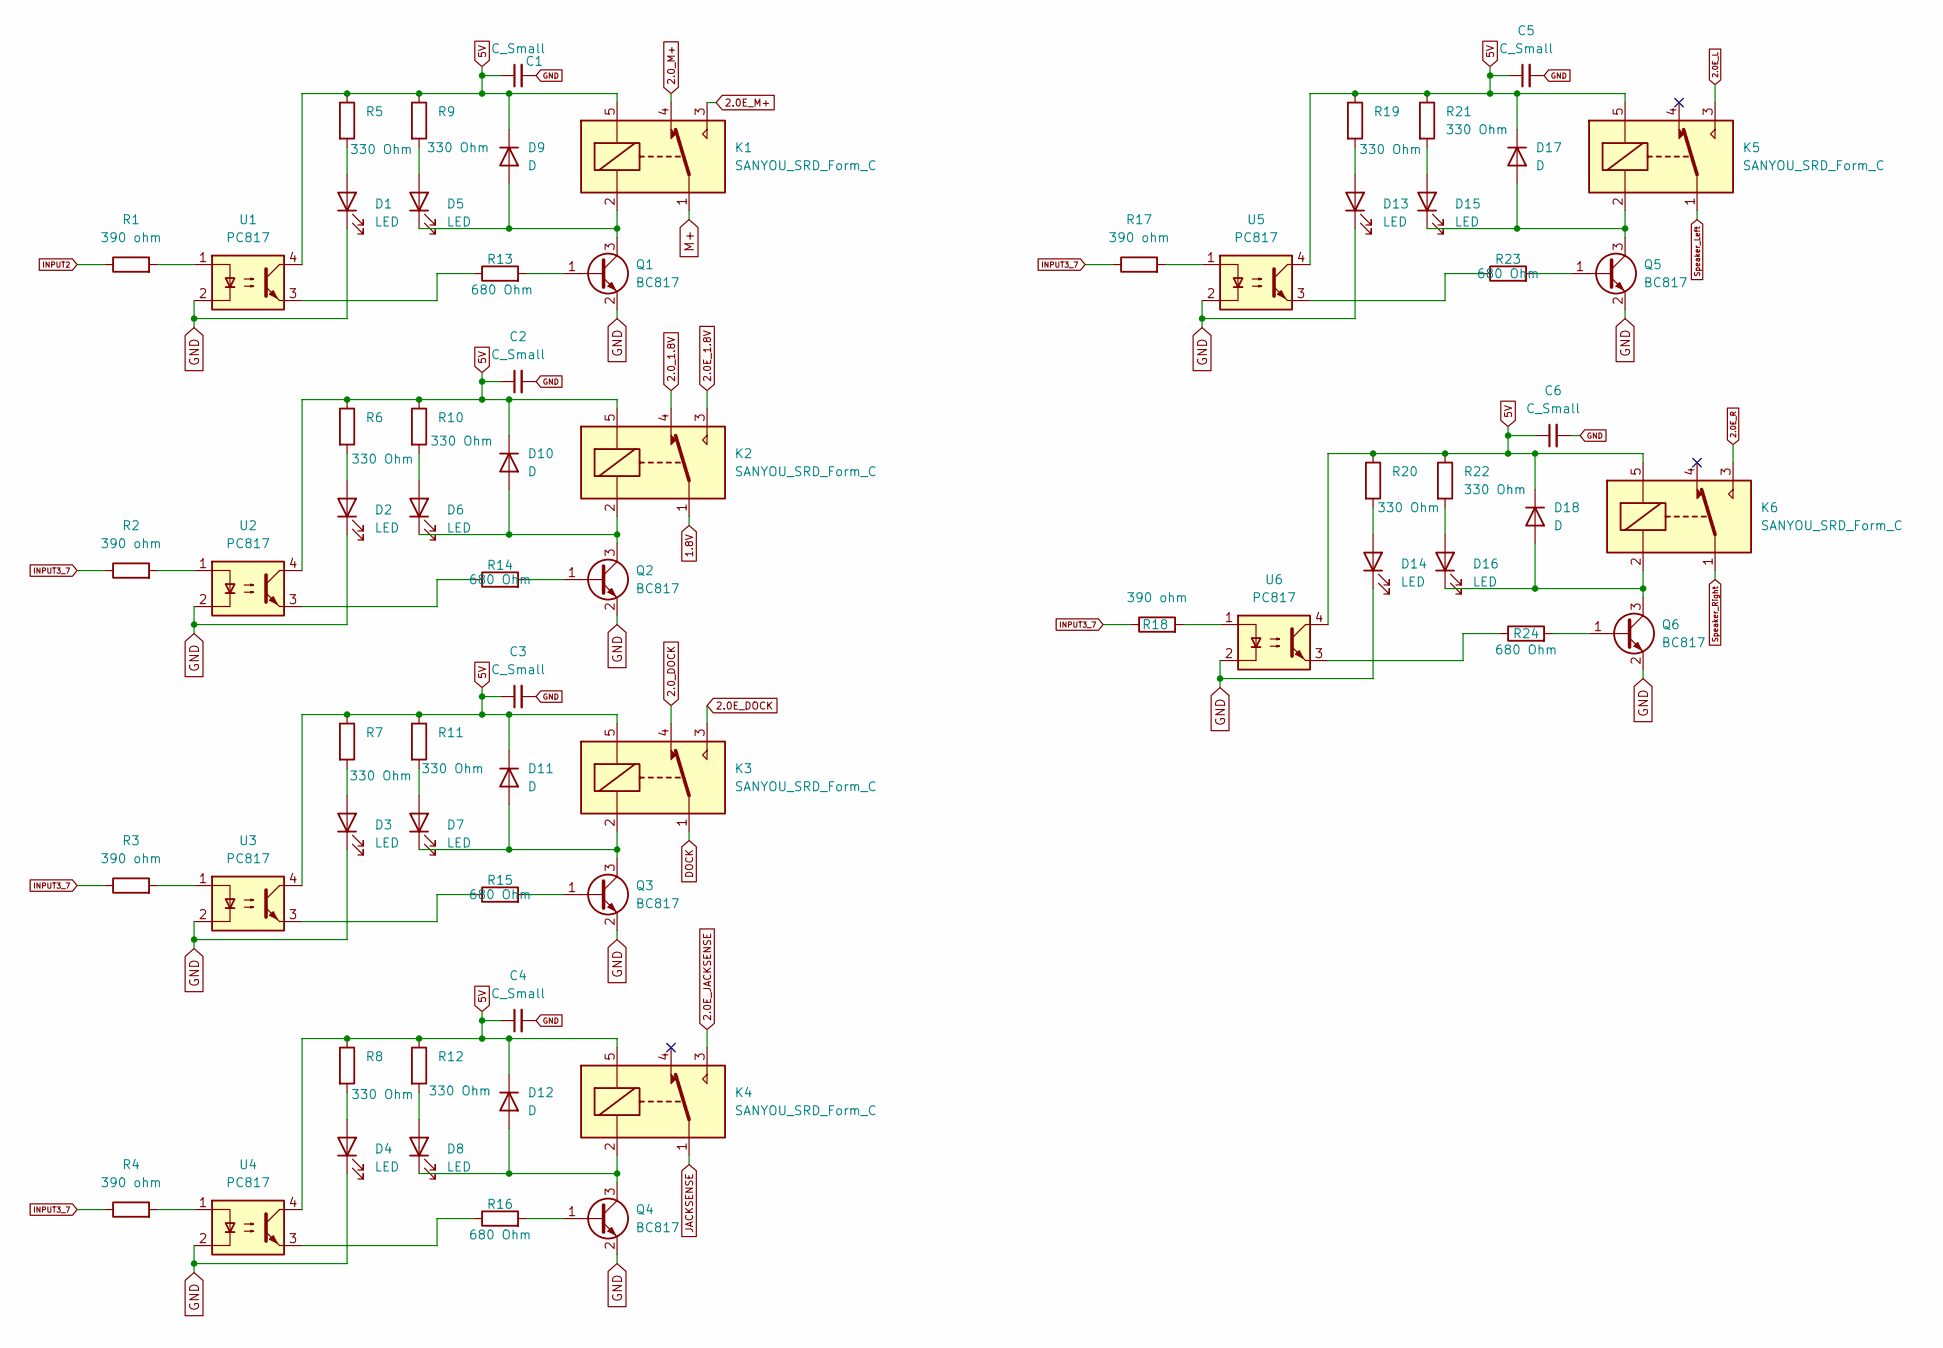
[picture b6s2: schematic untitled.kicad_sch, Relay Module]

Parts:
C1, C2, C3, C4, C5, C6: C_Small; GRM188R61A226ME15D; mpn GRM188R61A226ME15D
D1, D2, D3, D4, D5, D6, D7, D8, D13, D14, D15, D16: LED; LED_0603_1608Metric; mpn 19-21SURC/S530-A3/TR8
D9, D10, D11, D12, D17, D18: D; D_SOD-123; mpn RB751S40T1G
K1, K2, K3, K4, K5, K6: SANYOU_SRD_Form_C; Relay_SPDT_SANYOU_SRD_Series_Form_C; mpn SRD-05VDC-SL-C
Q1, Q2, Q3, Q4, Q5, Q6: BC817; SOT-23; mpn BC817
R1, R2, R3, R4, R17, R18: 390 ohm; R_0402_1005Metric; mpn RC0603FR-07390RL
R5, R6, R7, R8, R9, R10, R11, R12, R19, R20, R21, R22: 330 Ohm; R_0402_1005Metric; mpn CR-03FTP-330R
R13, R14, R15, R16, R23, R24: 680 Ohm; R_0402_1005Metric; mpn RC0603FR-07680RL
U1, U2, U3, U4, U5, U6: PC817; DIP-4_W7.62mm; mpn PC817

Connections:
1.8V: K2.1; also elsewhere on the board
2.0E_1.8V: K2.3; also elsewhere on the board
2.0E_DOCK: K3.3; also elsewhere on the board
2.0E_JACKSENSE: K4.3; also elsewhere on the board
2.0E_L: K5.3; also elsewhere on the board
2.0E_M+: K1.3; also elsewhere on the board
2.0E_R: K6.3; also elsewhere on the board
2.0_1.8V: K2.4; also elsewhere on the board
2.0_DOCK: K3.4; also elsewhere on the board
2.0_M+: K1.4; also elsewhere on the board
5V: C1.1, C2.1, C3.1, C4.1, C5.1, C6.1, D9.1 (K), D10.1 (K), D11.1 (K), D12.1 (K), D17.1 (K), D18.1 (K), K1.5, K2.5, K3.5, K4.5, K5.5, K6.5, R5.1, R6.1, R7.1, R8.1, R9.1, R10.1, R11.1, R12.1, R19.1, R20.1, R21.1, R22.1, U1.4, U2.4, U3.4, U4.4, U5.4, U6.4; also elsewhere on the board
DOCK: K3.1; also elsewhere on the board
GND: C1.2, C2.2, C3.2, C4.2, C5.2, C6.2, D1.1 (K), D2.1 (K), D3.1 (K), D4.1 (K), D13.1 (K), D14.1 (K), Q1.2 (E), Q2.2 (E), Q3.2 (E), Q4.2 (E), Q5.2 (E), Q6.2 (E), U1.2, U2.2, U3.2, U4.2, U5.2, U6.2; also elsewhere on the board
INPUT2: R1.1; also elsewhere on the board
INPUT3_7: R2.1, R3.1, R4.1, R17.1, R18.1; also elsewhere on the board
JACKSENSE: K4.1; also elsewhere on the board
M+: K1.1; also elsewhere on the board
unnamed: D1.2 (A), R5.2
unnamed: D2.2 (A), R6.2
unnamed: D3.2 (A), R7.2
unnamed: D4.2 (A), R8.2
unnamed: D5.2 (A), R9.2
unnamed: D5.1 (K), D9.2 (A), K1.2, Q1.3 (C)
unnamed: D6.2 (A), R10.2
unnamed: D7.2 (A), R11.2
unnamed: D8.2 (A), R12.2
unnamed: D6.1 (K), D10.2 (A), K2.2, Q2.3 (C)
unnamed: D7.1 (K), D11.2 (A), K3.2, Q3.3 (C)
unnamed: D8.1 (K), D12.2 (A), K4.2, Q4.3 (C)
unnamed: D13.2 (A), R19.2
unnamed: D14.2 (A), R20.2
unnamed: D15.2 (A), R21.2
unnamed: D15.1 (K), D17.2 (A), K5.2, Q5.3 (C)
unnamed: D16.2 (A), R22.2
unnamed: D16.1 (K), D18.2 (A), K6.2, Q6.3 (C)
unnamed: Q1.1 (B), R13.2
unnamed: Q2.1 (B), R14.2
unnamed: Q3.1 (B), R15.2
unnamed: Q4.1 (B), R16.2
unnamed: Q5.1 (B), R23.2
unnamed: Q6.1 (B), R24.2
unnamed: R1.2, U1.1
unnamed: R2.2, U2.1
unnamed: R3.2, U3.1
unnamed: R4.2, U4.1
unnamed: R13.1, U1.3
unnamed: R14.1, U2.3
unnamed: R15.1, U3.3
unnamed: R16.1, U4.3
unnamed: R17.2, U5.1
unnamed: R18.2, U6.1
unnamed: R23.1, U5.3
unnamed: R24.1, U6.3
Speaker_Left: K5.1; also elsewhere on the board
Speaker_Right: K6.1; also elsewhere on the board

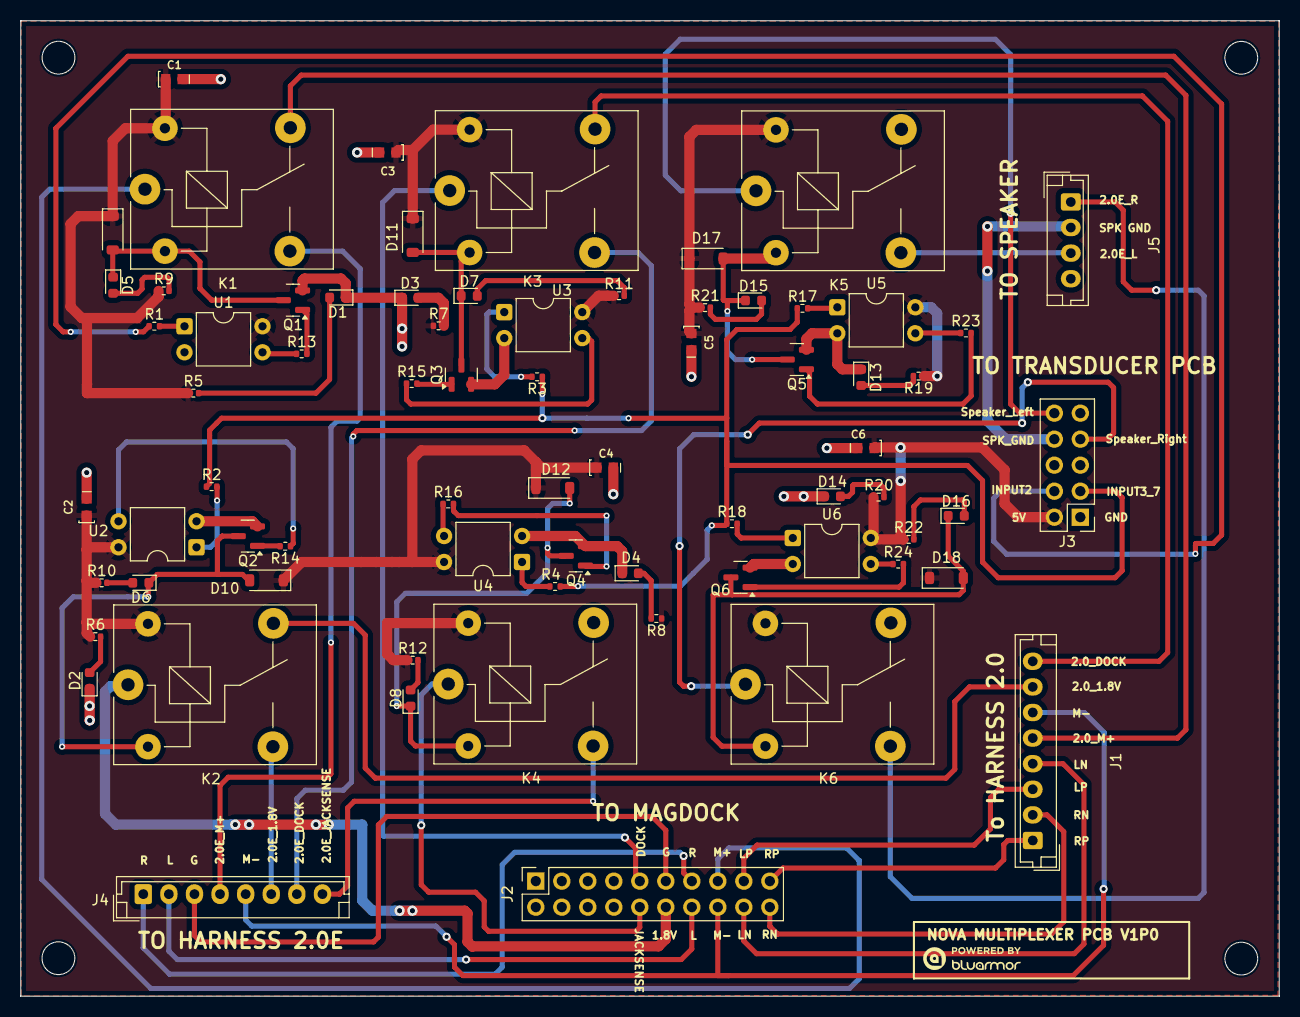
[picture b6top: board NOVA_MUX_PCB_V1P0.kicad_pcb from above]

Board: 2 copper layers, 122.9 x 95.3 mm, 75 parts (0 on the bottom side), 64 nets.
